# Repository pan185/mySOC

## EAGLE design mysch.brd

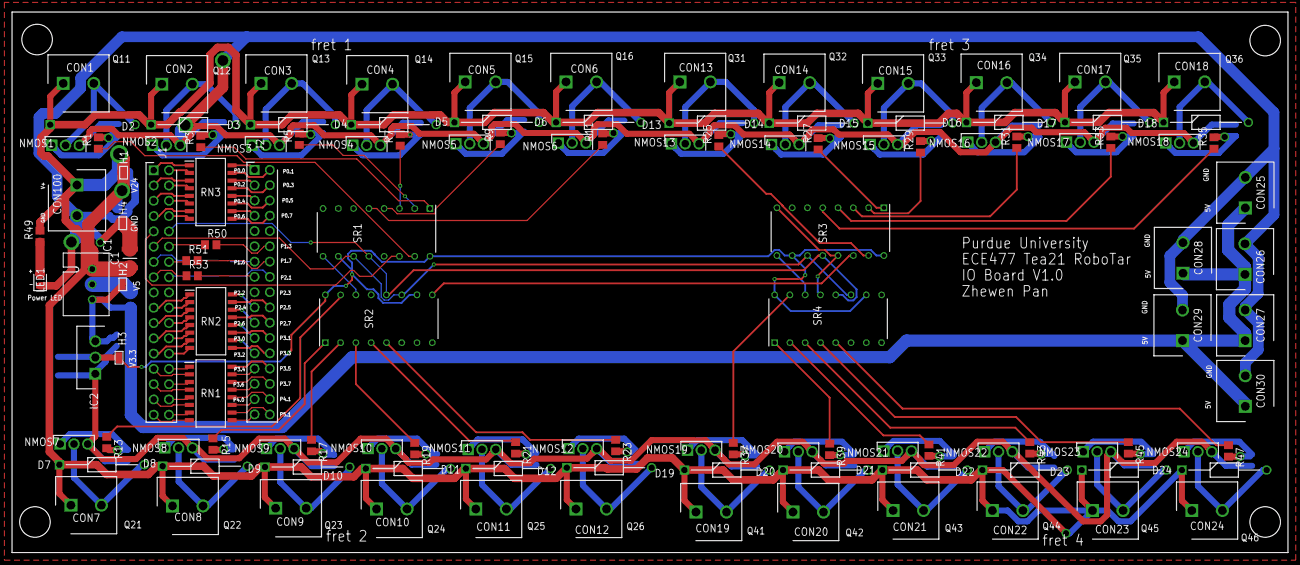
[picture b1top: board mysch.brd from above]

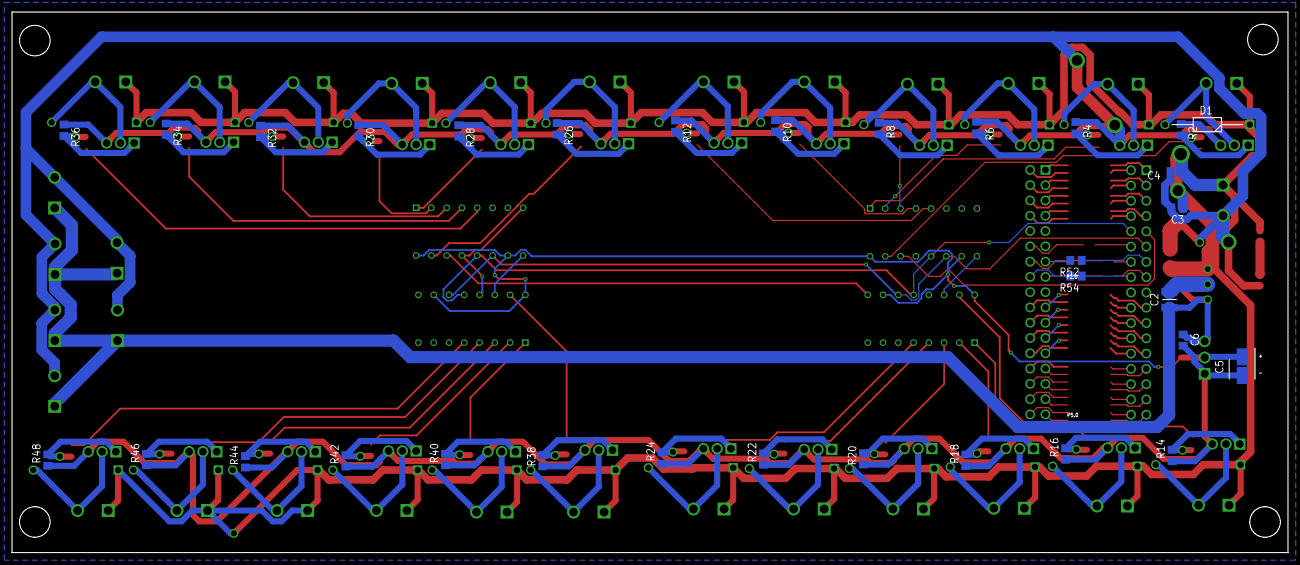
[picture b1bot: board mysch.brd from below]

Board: 2 copper layers, 212.1 x 89.8 mm, 155 parts (32 on the bottom side), 141 nets.

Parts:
C1: 10u; CAPC3225X270N
C2: 22u; CAPC3225X270N
C3: 1u; C0805
C4: 0.1u; C0805
C5: 865080540004; CAPAE430X550N
C6: 100n; C0805
CON1, CON2, CON3, CON4, CON5, CON6, CON7, CON8, CON9, CON10, CON11, CON12, CON13, CON14, CON15, CON16, CON17, CON18, CON19, CON20, CON21, CON22, CON23, CON24, CON25, CON26, CON27, CON28, CON29, CON30, CON100: 1888687; SHDR2W90P0X508_1X2_1016X950X15
D1, D2, D3, D4, D5, D6, D7, D8, D9, D10, D11, D12, D13, D14, D15, D16, D17, D18, D19, D20, D21, D22, D23, D24: 1N4007; DIOAD1410W86L470D235
H1, H2, H3, H4: S2761-46R; S276146R
IC1: OKI-78SR-5_1.5-W36-C; OKI-78SR
IC2: LD1117AV33; TO270P460X1020X2008-3P
J1, J2: 90131-0937; HDRV34W90P254_2X17_4308X500X56
LED1: SML-H12U8TT86C; LEDC2012X90N
NMOS1, NMOS2, NMOS3, NMOS4, NMOS5, NMOS6, NMOS7, NMOS8, NMOS9, NMOS10, NMOS11, NMOS12, NMOS13, NMOS14, NMOS15, NMOS16, NMOS17, NMOS18, NMOS19, NMOS20, NMOS21, NMOS22, NMOS23, NMOS24: RFD3055LE; TO229P250X658X985-3P
R1, R3, R5, R7, R9, R11, R13, R15, R17, R19, R21, R23, R25, R27, R29, R31, R33, R35, R37, R39, R41, R43, R45, R47: 1M; R0805
R2, R4, R6, R8, R10, R12, R14, R16, R18, R20, R22, R24, R26, R28, R30, R32, R34, R36, R38, R40, R42, R44, R46, R48: 3.3k; R0805
R49: 1.1k; R0805
R50, R51, R52, R53, R54: 100; R0805
RN1, RN2, RN3: 4816P-T01-101LF; SOIC127P762X215-16N
SR1, SR2, SR3, SR4: SN74HC595N; DIP794W53P254L1930H508Q16N

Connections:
GND: C1.1, C2.1, C3.2, C4.2, C5.2, C6.2, CON25.2, CON26.2, CON27.2, CON28.2, CON29.2, CON30.2, CON100.2, H4.1, IC1.2, IC2.1, LED1.1, NMOS1.3, NMOS2.3, NMOS3.3, NMOS4.3, NMOS5.3, NMOS6.3, NMOS7.3, NMOS8.3, NMOS9.3, NMOS10.3, NMOS11.3, NMOS12.3, NMOS13.3, NMOS14.3, NMOS15.3, NMOS16.3, NMOS17.3, NMOS18.3, NMOS19.3, NMOS20.3, NMOS21.3, NMOS22.3, NMOS23.3, NMOS24.3, R2.1, R4.1, R6.1, R8.1, R10.1, R12.1, R14.1, R16.1, R18.1, R20.1, R22.1, R24.1, R26.1, R28.1, R30.1, R32.1, R34.1, R36.1, R38.1, R40.1, R42.1, R44.1, R46.1, R48.1, SR1.8, SR1.13, SR2.8, SR2.13, SR3.8, SR3.13, SR4.8, SR4.13
unnamed: CON11.2, D11.2, NMOS11.2
unnamed: NMOS11.1, R21.2, R22.2
unnamed: CON12.2, D12.2, NMOS12.2
unnamed: NMOS12.1, R23.2, R24.2
unnamed: CON14.2, D14.2, NMOS14.2
unnamed: NMOS1.1, R1.2, R2.2
unnamed: CON1.2, D1.2, NMOS1.2
unnamed: CON13.2, D13.2, NMOS13.2
unnamed: NMOS14.1, R27.2, R28.2
unnamed: CON15.2, D15.2, NMOS15.2
unnamed: CON2.2, D2.2, NMOS2.2
unnamed: NMOS2.1, R3.2, R4.2
unnamed: NMOS15.1, R29.2, R30.2
unnamed: CON3.2, D3.2, NMOS3.2
unnamed: NMOS3.1, R5.2, R6.2
unnamed: CON16.2, D16.2, NMOS16.2
unnamed: CON4.2, D4.2, NMOS4.2
unnamed: NMOS4.1, R7.2, R8.2
unnamed: NMOS16.1, R31.2, R32.2
unnamed: CON5.2, D5.2, NMOS5.2
unnamed: NMOS5.1, R9.2, R10.2
unnamed: CON17.2, D17.2, NMOS17.2
unnamed: CON6.2, D6.2, NMOS6.2
unnamed: NMOS6.1, R11.2, R12.2
unnamed: NMOS17.1, R33.2, R34.2
unnamed: CON7.2, D7.2, NMOS7.2
unnamed: NMOS7.1, R13.2, R14.2
unnamed: CON18.2, D18.2, NMOS18.2
unnamed: CON8.2, D8.2, NMOS8.2
unnamed: NMOS8.1, R15.2, R16.2
unnamed: NMOS18.1, R35.2, R36.2
unnamed: CON9.2, D9.2, NMOS9.2
unnamed: NMOS9.1, R17.2, R18.2
unnamed: CON19.2, D19.2, NMOS19.2
unnamed: CON10.2, D10.2, NMOS10.2
unnamed: NMOS10.1, R19.2, R20.2
unnamed: NMOS19.1, R37.2, R38.2
unnamed: CON20.2, D20.2, NMOS20.2
unnamed: NMOS20.1, R39.2, R40.2
unnamed: CON21.2, D21.2, NMOS21.2
unnamed: NMOS21.1, R41.2, R42.2
unnamed: CON22.2, D22.2, NMOS22.2
unnamed: NMOS22.1, R43.2, R44.2
unnamed: NMOS13.1, R25.2, R26.2
unnamed: CON23.2, D23.2, NMOS23.2
unnamed: NMOS23.1, R45.2, R46.2
unnamed: CON24.2, D24.2, NMOS24.2
unnamed: NMOS24.1, R47.2, R48.2
unnamed: LED1.2, R49.1
OUT1: SR1.9, SR2.14
OUT2: SR2.9, SR3.14
OUT3: SR3.9, SR4.14
P0.0: J1.1, RN3.1
P0.0_O: J2.1, RN3.16
P0.1: J1.2, RN3.2
P0.1_O: J2.2, RN3.15
P0.2: J1.3, RN3.3
P0.2_O: J2.3, RN3.14
P0.3: J1.4, RN3.4
P0.3_O: J2.4, RN3.13
P0.4: J1.5, RN3.5
P0.4_O: J2.5, RN3.12
P0.5: J1.6, RN3.6
P0.5_O: J2.6, RN3.11
P0.6: J1.7, RN3.7
P0.6_O: J2.7, RN3.10
P0.7: J1.8, RN3.8
P0.7_O: J2.8, RN3.9
P1.0: J1.9, SR1.14
P1.1: J1.10, SR1.12, SR2.12, SR3.12, SR4.12
P1.2: J1.11, SR1.11, SR2.11, SR3.11, SR4.11
P1.3: J1.12, R50.1
P1.3_O: J2.12, R50.2
P1.6: J1.13, R52.1
P1.6_O: J2.13, R52.2
P1.7: J1.14, R51.1
P1.7_O: J2.14, R51.2
P2.0: J1.15, R53.1
P2.0_O: J2.15, R53.2
P2.1: J1.16, R54.1
P2.1_O: J2.16, R54.2
P2.4: J1.19, RN2.1
P2.4_O: J2.19, RN2.16
P2.5: J1.20, RN2.2
P2.5_O: J2.20, RN2.15
P2.6: J1.21, RN2.3
P2.6_O: J2.21, RN2.14
P2.7: J1.22, RN2.4
P2.7_O: J2.22, RN2.13
P3.0: J1.23, RN2.5
P3.0_O: J2.23, RN2.12
P3.1: J1.24, RN2.6
P3.1_O: J2.24, RN2.11
P3.2: J1.25, RN2.7
P3.2_O: J2.25, RN2.10
P3.3: J1.26, RN2.8
P3.3_O: J2.26, RN2.9
P3.4: J1.27, RN1.2
P3.4_O: J2.27, RN1.15
P3.5: J1.28, RN1.1
P3.5_O: J2.28, RN1.16
P3.6: J1.29, RN1.4
P3.6_O: J2.29, RN1.13
P3.7: J1.30, RN1.3
P3.7_O: J2.30, RN1.14
P4.0: J1.31, RN1.6
P4.0_O: J2.31, RN1.11
P4.1: J1.32, RN1.5
P4.1_O: J2.32, RN1.12
P5.0: J1.33, RN1.8
P5.0_O: J2.33, RN1.9
P5.1: J1.34, RN1.7
P5.1_O: J2.34, RN1.10
Q11: R1.1, SR1.15
Q12: R3.1, SR1.1
Q13: R5.1, SR1.2
Q14: R7.1, SR1.3
Q15: R9.1, SR1.4
Q16: R11.1, SR1.5
Q21: R13.1, SR2.15
Q22: R15.1, SR2.1
Q23: R17.1, SR2.2
Q24: R19.1, SR2.3
Q25: R21.1, SR2.4
Q26: R23.1, SR2.5
Q31: R25.1, SR3.15
Q32: R27.1, SR3.1
Q33: R29.1, SR3.2
Q34: R31.1, SR3.3
Q35: R33.1, SR3.4
Q36: R35.1, SR3.5
Q41: R37.1, SR4.15
Q42: R39.1, SR4.1
Q43: R41.1, SR4.2
Q44: R43.1, SR4.3
Q45: R45.1, SR4.4
Q46: R47.1, SR4.5
V3.3: C5.1, H3.1, IC2.2, SR1.10, SR1.16, SR2.10, SR2.16, SR3.10, SR3.16, SR4.10, SR4.16
V5: C2.2, C6.1, CON25.1, CON26.1, CON27.1, CON28.1, CON29.1, CON30.1, H2.1, IC1.3, IC2.3
V24: C1.2, C3.1, C4.1, CON1.1, CON2.1, CON3.1, CON4.1, CON5.1, CON6.1, CON7.1, CON8.1, CON9.1, CON10.1, CON11.1, CON12.1, CON13.1, CON14.1, CON15.1, CON16.1, CON17.1, CON18.1, CON19.1, CON20.1, CON21.1, CON22.1, CON23.1, CON24.1, CON100.1, D1.1, D2.1, D3.1, D4.1, D5.1, D6.1, D7.1, D8.1, D9.1, D10.1, D11.1, D12.1, D13.1, D14.1, D15.1, D16.1, D17.1, D18.1, D19.1, D20.1, D21.1, D22.1, D23.1, D24.1, H1.1, IC1.1, R49.2

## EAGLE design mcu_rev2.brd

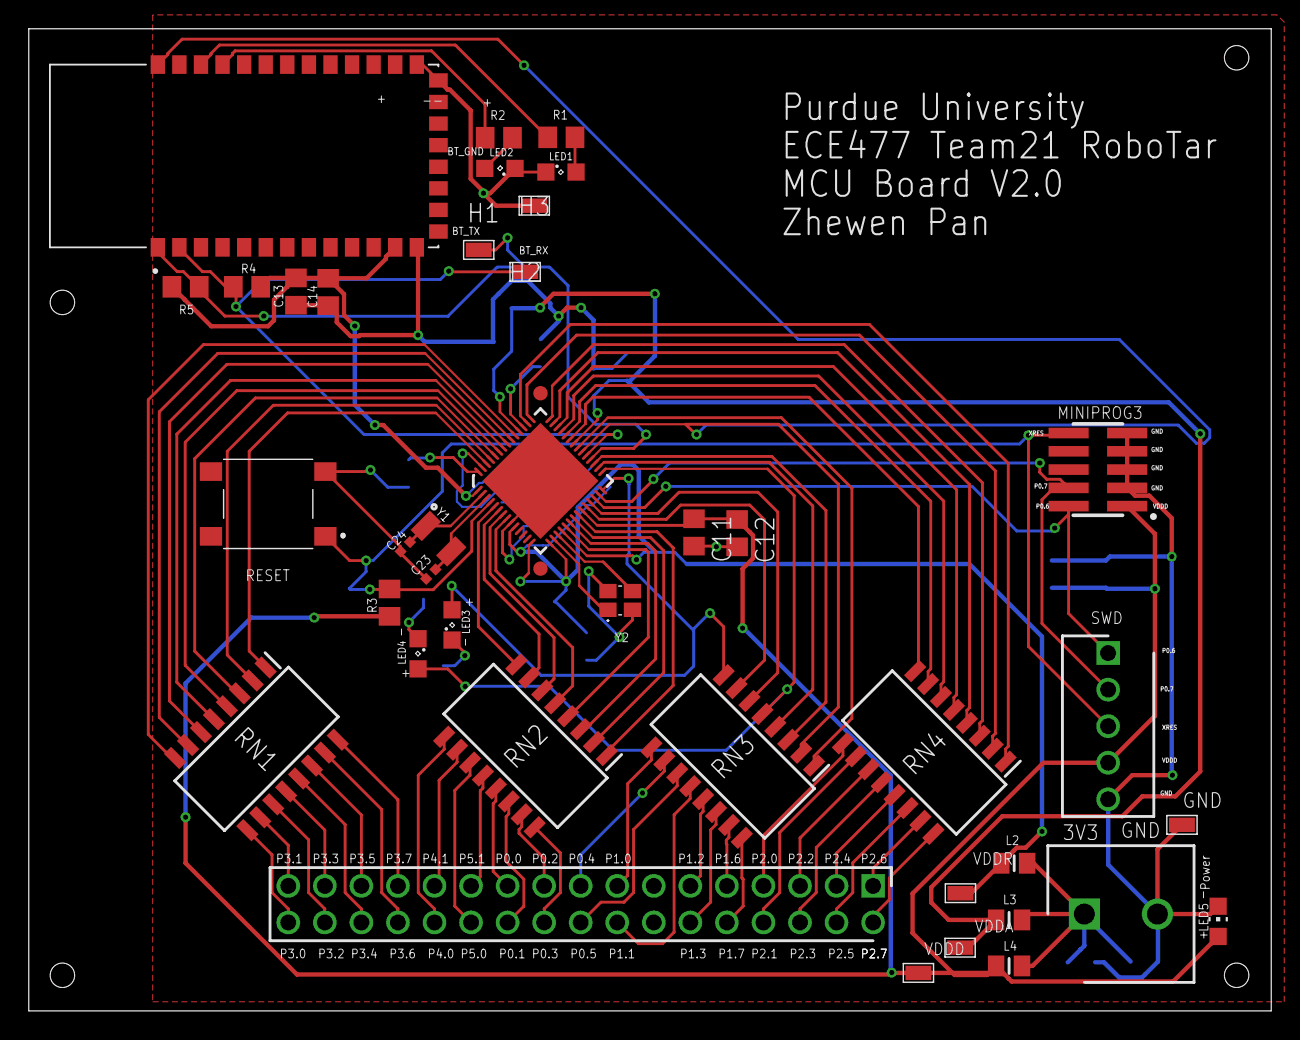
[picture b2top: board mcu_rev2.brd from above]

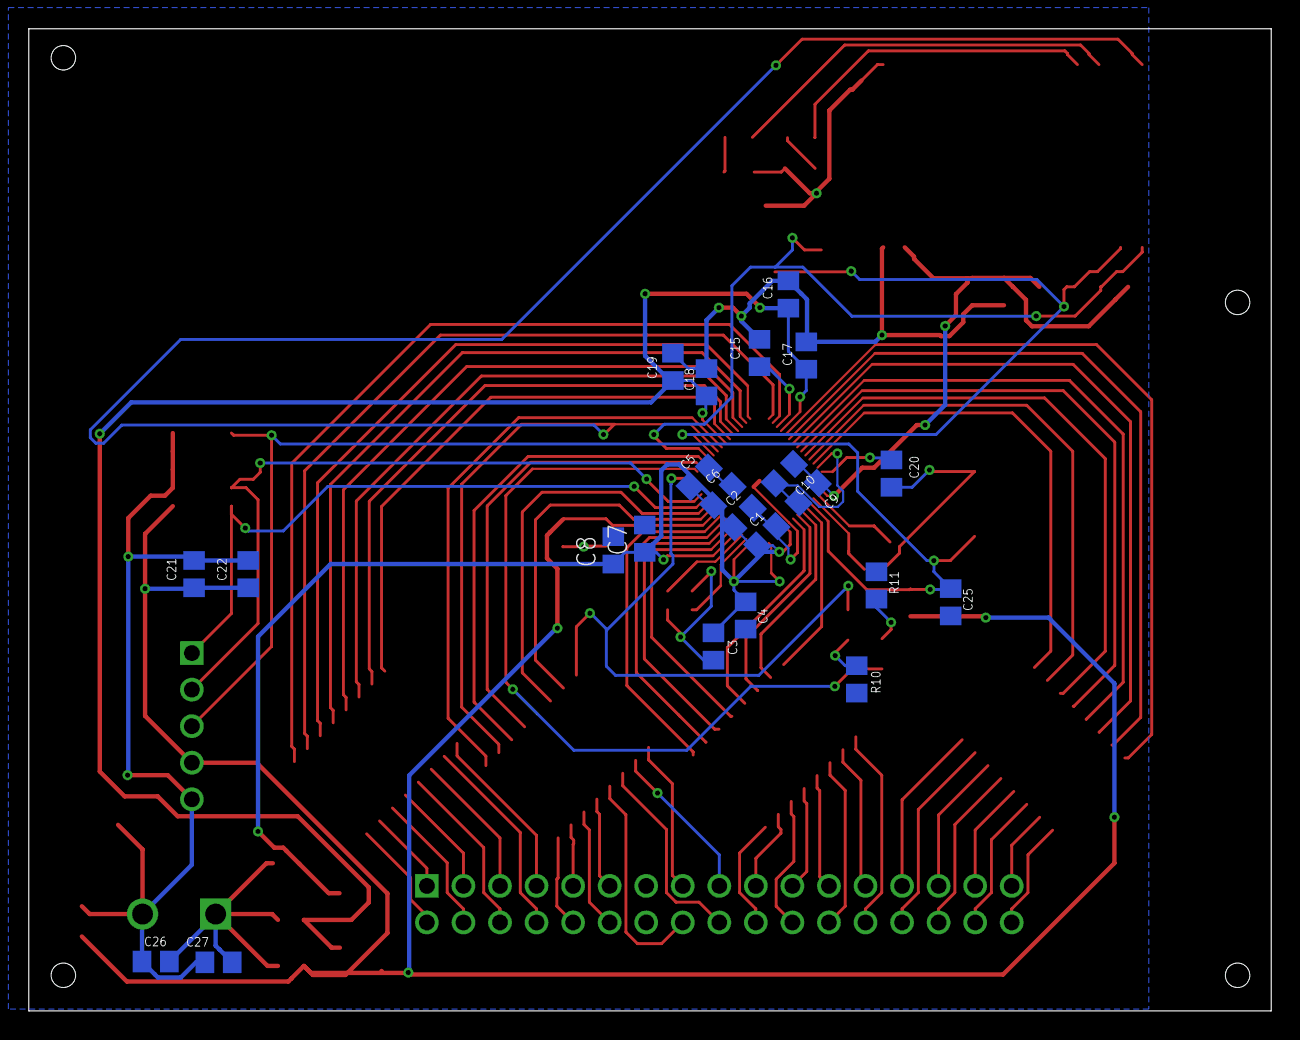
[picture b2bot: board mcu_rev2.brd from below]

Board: 2 copper layers, 86.3 x 68.2 mm, 62 parts (23 on the bottom side), 86 nets.

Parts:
BT_SLAVE: HC-05; XCVR_HC-05
C1, C3, C5, C7, C9, C11, C13, C16, C18, C21, C27: 0.1u; C0805
C2, C4, C6, C8, C10, C12, C14, C17, C19, C20, C22, C26: 1u; C0805
C15: 1uF; C0805
C23: 36p; CAPC1005X55N
C24: 18p; CAPC1005X55N
C25: 100p; C0805
CON1: 1888687; SHDR2W90P0X508_1X2_1016X950X15
H1, H2, H3, H4, H5, H6, H7: S2761-46R; S276146R
IC1: CY8C4248LQI-BL583; QFN40P700X700X60-57N
J1: MINIPROG3; FTSH-105-01-L-DV-K
J2: SWD; HDRV5W64P0X254_1X5_1255X635X81
J3: 90131-0937; HDRV34W90P254_2X17_4308X500X56
L2, L3, L4: 330ohm, 100MHz; BEADC2012X105N
LED1, LED2, LED3, LED4: 0; SML0805
LED5: 0; CHIP-LED0805
R1, R2: 470; R0805
R3, R4: 4.7k; R0805
R5: 10k; R0805
R10, R11: 1.5k; R0805
RN1, RN2, RN3, RN4: 4816P-T01-101LF; SOIC127P762X215-16N
S1: DTSM-63N-V-B; DTSM63NVB
Y1: 32.768KHz; ECX-31B
Y2: 24MHz; ECS240836QAESTR

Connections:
3V3: C26.1, C27.1, CON1.1, L2.1, L3.1, L4.1
/XRES: C25.1, IC1.4, J1.10, J2.3, R3.1, S1.1
GND: BT_SLAVE.13, BT_SLAVE.21, BT_SLAVE.22, C1.2, C2.2, C3.2, C4.2, C5.2, C6.2, C7.2, C8.2, C9.2, C10.2, C11.2, C12.2, C13.2, C14.2, C15.2, C16.2, C17.2, C18.2, C19.2, C20.2, C21.2, C22.2, C23.1, C24.1, C25.2, C26.2, C27.2, CON1.2, H3.1, H7.1, IC1.9, IC1.55, IC1.57, J1.3, J1.5, J1.7, J1.9, J2.5, LED1.C, LED2.C, LED5.C, R10.2, R11.2, S1.3, Y2.2, Y2.4
IND1: BT_SLAVE.32, R1.1
IND2: BT_SLAVE.31, R2.1
MID1: LED1.A, R1.2
MID2: LED2.A, R2.2
unnamed: LED3.C, R10.1
unnamed: LED4.C, R11.1
P0.0: IC1.19, RN2.4
P0.0_O: J3.21, RN2.13
P0.1: IC1.20, RN2.3
P0.1_O: J3.22, RN2.14
P0.2: IC1.21, RN2.2
P0.2_O: J3.19, RN2.15
P0.3: IC1.22, RN2.1
P0.3_O: J3.20, RN2.16
P0.4: IC1.24, RN3.7
P0.4_O: J3.17, RN3.10
P0.5: IC1.25, RN3.6
P0.5_O: J3.18, RN3.11
P0.6: IC1.26, J1.2, J2.1
P0.7: IC1.27, J1.4, J2.2
P1.0: IC1.28, LED3.A, RN3.8
P1.0_O: J3.15, RN3.9
P1.1: IC1.29, LED4.A, RN3.5
P1.1_O: J3.16, RN3.12
P1.2: IC1.30, RN3.4
P1.2_O: J3.11, RN3.13
P1.3: IC1.31, RN3.3
P1.3_O: J3.12, RN3.14
P1.4: BT_SLAVE.1, H1.1, IC1.32, R5.1
P1.5: BT_SLAVE.2, H2.1, IC1.33, R4.1
P1.6: BT_SLAVE.34, IC1.34, RN3.2
P1.6_O: J3.9, RN3.15
P1.7: IC1.35, RN3.1
P1.7_O: J3.10, RN3.16
P2.0: IC1.37, RN4.8
P2.0_O: J3.7, RN4.9
P2.1: IC1.38, RN4.7
P2.1_O: J3.8, RN4.10
P2.2: IC1.39, RN4.6
P2.2_O: J3.5, RN4.11
P2.3: IC1.40, RN4.5
P2.3_O: J3.6, RN4.12
P2.4: IC1.41, RN4.4
P2.4_O: J3.3, RN4.13
P2.5: IC1.42, RN4.3
P2.5_O: J3.4, RN4.14
P2.6: IC1.43, RN4.2
P2.6_O: J3.1, RN4.15
P2.7: IC1.44, RN4.1
P2.7_O: J3.2, RN4.16
P3.0: IC1.47, RN1.8
P3.0_O: J3.34, RN1.9
P3.1: IC1.48, RN1.7
P3.1_O: J3.33, RN1.10
P3.2: IC1.49, RN1.6
P3.2_O: J3.32, RN1.11
P3.3: IC1.50, RN1.5
P3.3_O: J3.31, RN1.12
P3.4: IC1.51, RN1.4
P3.4_O: J3.30, RN1.13
P3.5: IC1.52, RN1.3
P3.5_O: J3.29, RN1.14
P3.6: IC1.53, RN1.2
P3.6_O: J3.28, RN1.15
P3.7: IC1.54, RN1.1
P3.7_O: J3.27, RN1.16
P4.0: IC1.5, RN2.8
P4.0_O: J3.26, RN2.9
P4.1: IC1.6, RN2.7
P4.1_O: J3.25, RN2.10
P5.0: IC1.7, RN2.6
P5.0_O: J3.24, RN2.11
P5.1: IC1.8, RN2.5
P5.1_O: J3.23, RN2.12
P6.0: C24.2, IC1.2, Y1.1
P6.1: C23.2, IC1.3, Y1.2
VCCD: C20.1, IC1.56
VDDA: C16.1, C17.1, C18.1, C19.1, H5.1, IC1.36, IC1.46, L3.2
VDDD: BT_SLAVE.12, C9.1, C10.1, C11.1, C12.1, C13.1, C14.1, C21.1, C22.1, H4.1, IC1.1, IC1.23, J1.1, J2.4, L4.2, LED5.A, R3.2, R4.2, R5.2
VDDR: C1.1, C2.1, C3.1, C4.1, C5.1, C6.1, C7.1, C8.1, H6.1, IC1.10, IC1.14, IC1.15, IC1.18, L2.2
VREF: C15.1, IC1.45
XTAL24I: IC1.16, Y2.1
XTAL24O: IC1.17, Y2.3

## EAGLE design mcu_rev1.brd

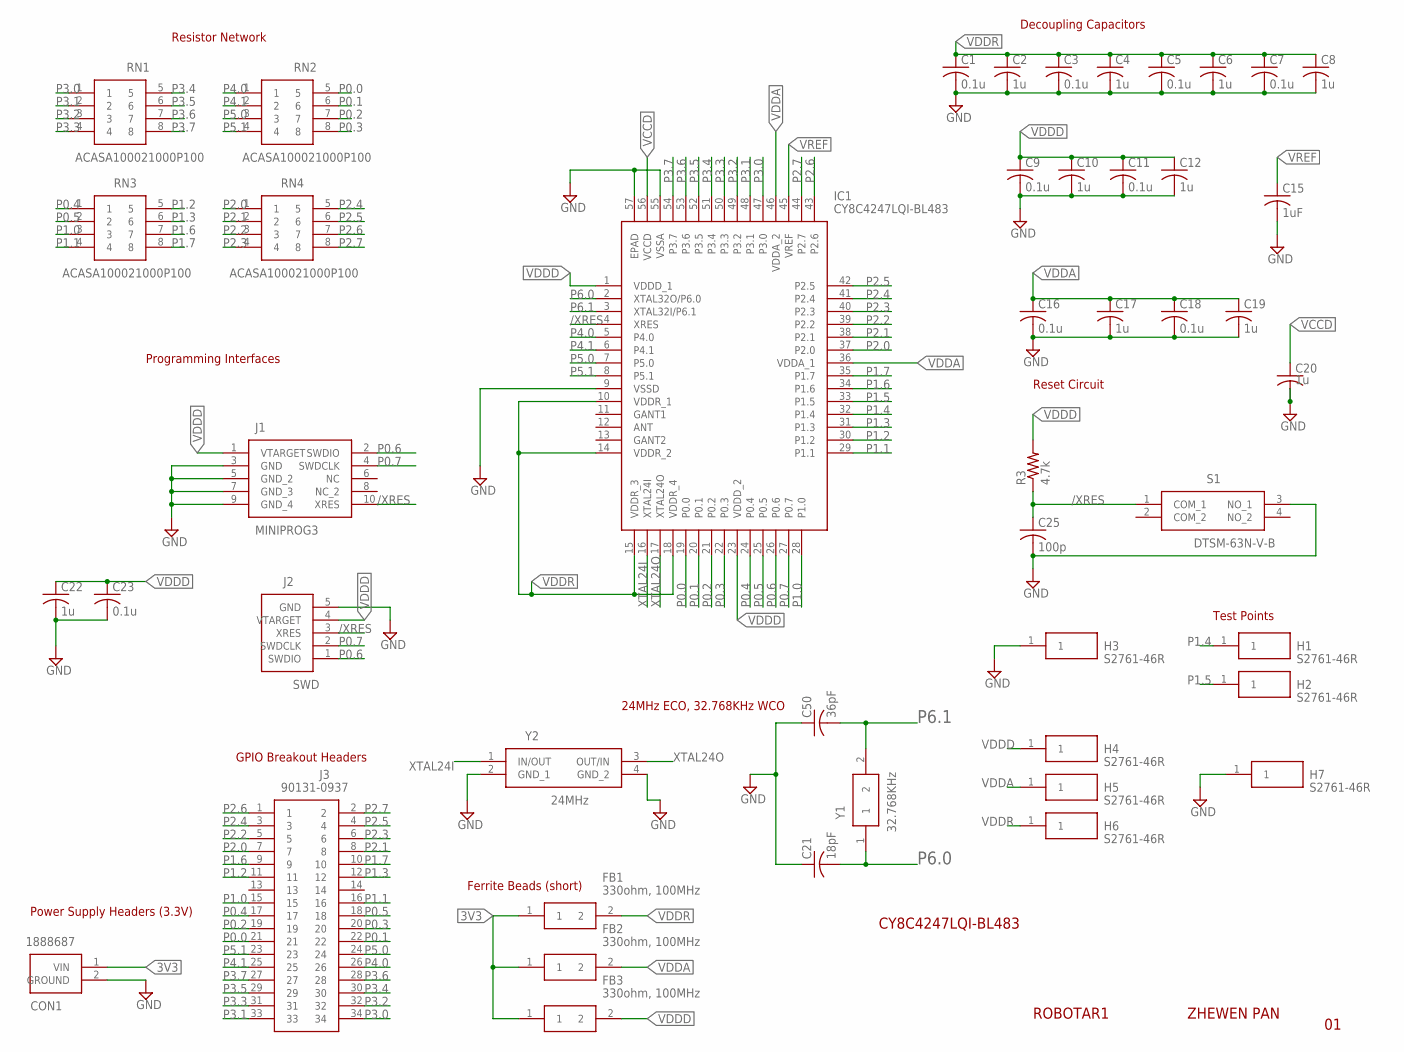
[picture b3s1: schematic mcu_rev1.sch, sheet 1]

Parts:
C1, C3, C5, C7, C9, C11, C16, C18, C23: 0.1u; C0805
C2, C4, C6, C8, C10, C12, C17, C19, C20, C22: 1u; C0805
C15: 1uF; C0805
C21: 18pF; C0805
C25: 100p; C0805
C50: 36pF; C0805
CON1: 1888687; SHDR2W90P0X508_1X2_1016X950X15
FB1, FB2, FB3: 330ohm, 100MHz; BEADC2012X105N
H1, H2, H3, H4, H5, H6, H7: S2761-46R; S276146R
IC1: CY8C4247LQI-BL483; QFN40P700X700X60-57N
J1: MINIPROG3; FTSH-105-01-L-DV-K
J2: SWD; HDRV5W64P0X254_1X5_1255X635X81
J3: 90131-0937; HDRV34W90P254_2X17_4308X500X56
R3: 4.7k; R0805
RN1, RN2, RN3, RN4: ACASA100021000P100
S1: DTSM-63N-V-B; DTSM63NVB
Y1: 32.768KHz; ECX-31B
Y2: 24MHz; ECS240836QAESTR

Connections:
3V3: CON1.1 (VIN), FB1.1, FB2.1, FB3.1
/XRES: C25.1, IC1.4 (XRES), J1.10 (XRES), J2.3 (XRES), R3.1, S1.1 (COM_1)
GND: C1.2, C2.2, C3.2, C4.2, C5.2, C6.2, C7.2, C8.2, C9.2, C10.2, C11.2, C12.2, C15.2, C16.2, C17.2, C18.2, C19.2, C20.2, C21.1, C22.2, C23.2, C25.2, C50.1, CON1.2 (GROUND), H3.1, H7.1, IC1.9 (VSSD), IC1.55 (VSSA), IC1.57 (EPAD), J1.3 (GND), J1.5 (GND_2), J1.7 (GND_3), J1.9 (GND_4), J2.5 (GND), S1.3 (NO_1), Y2.2 (GND_1), Y2.4 (GND_2); also elsewhere on the board
P0.0: IC1.19 (P0.0), J3.21, RN2.5
P0.1: IC1.20 (P0.1), J3.22, RN2.6
P0.2: IC1.21 (P0.2), J3.19, RN2.7
P0.3: IC1.22 (P0.3), J3.20, RN2.8
P0.4: IC1.24 (P0.4), J3.17, RN3.1
P0.5: IC1.25 (P0.5), J3.18, RN3.2
P0.6: IC1.26 (P0.6), J1.2 (SWDIO), J2.1 (SWDIO)
P0.7: IC1.27 (P0.7), J1.4 (SWDCLK), J2.2 (SWDCLK)
P1.0: IC1.28 (P1.0), J3.15, RN3.3
P1.1: IC1.29 (P1.1), J3.16, RN3.4
P1.2: IC1.30 (P1.2), J3.11, RN3.5
P1.3: IC1.31 (P1.3), J3.12, RN3.6
P1.4: H1.1, IC1.32 (P1.4); also elsewhere on the board
P1.5: H2.1, IC1.33 (P1.5); also elsewhere on the board
P1.6: IC1.34 (P1.6), J3.9, RN3.7; also elsewhere on the board
P1.7: IC1.35 (P1.7), J3.10, RN3.8
P2.0: IC1.37 (P2.0), J3.7, RN4.1
P2.1: IC1.38 (P2.1), J3.8, RN4.2
P2.2: IC1.39 (P2.2), J3.5, RN4.3
P2.3: IC1.40 (P2.3), J3.6, RN4.4
P2.4: IC1.41 (P2.4), J3.3, RN4.5
P2.5: IC1.42 (P2.5), J3.4, RN4.6
P2.6: IC1.43 (P2.6), J3.1, RN4.7
P2.7: IC1.44 (P2.7), J3.2, RN4.8
P3.0: IC1.47 (P3.0), J3.34, RN1.1
P3.1: IC1.48 (P3.1), J3.33, RN1.2
P3.2: IC1.49 (P3.2), J3.32, RN1.3
P3.3: IC1.50 (P3.3), J3.31, RN1.4
P3.4: IC1.51 (P3.4), J3.30, RN1.5
P3.5: IC1.52 (P3.5), J3.29, RN1.6
P3.6: IC1.53 (P3.6), J3.28, RN1.7
P3.7: IC1.54 (P3.7), J3.27, RN1.8
P4.0: IC1.5 (P4.0), J3.26, RN2.1
P4.1: IC1.6 (P4.1), J3.25, RN2.2
P5.0: IC1.7 (P5.0), J3.24, RN2.3
P5.1: IC1.8 (P5.1), J3.23, RN2.4
P6.0: C21.2, IC1.2 (XTAL32O/P6.0), Y1.1
P6.1: C50.2, IC1.3 (XTAL32I/P6.1), Y1.2
VCCD: C20.1, IC1.56 (VCCD)
VDDA: C16.1, C17.1, C18.1, C19.1, FB2.2, H5.1, IC1.36 (VDDA_1), IC1.46 (VDDA_2)
VDDD: C9.1, C10.1, C11.1, C12.1, C22.1, C23.1, FB3.2, H4.1, IC1.1 (VDDD_1), IC1.23 (VDDD_2), J1.1 (VTARGET), J2.4 (VTARGET), R3.2; also elsewhere on the board
VDDR: C1.1, C2.1, C3.1, C4.1, C5.1, C6.1, C7.1, C8.1, FB1.2, H6.1, IC1.10 (VDDR_1), IC1.14 (VDDR_2), IC1.15 (VDDR_3), IC1.18 (VDDR_4)
VREF: C15.1, IC1.45 (VREF)
XTAL24I: IC1.16 (XTAL24I), Y2.1 (IN/OUT)
XTAL24O: IC1.17 (XTAL24O), Y2.3 (OUT/IN)

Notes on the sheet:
CY8C4247LQI-BL483
ROBOTAR1
ZHEWEN PAN
Programming Interfaces
GPIO Breakout Headers
Power Supply Headers (3.3V)
Ferrite Beads (short)
24MHz ECO, 32.768KHz WCO
Reset Circuit
Test Points
Resistor Network
Decoupling Capacitors

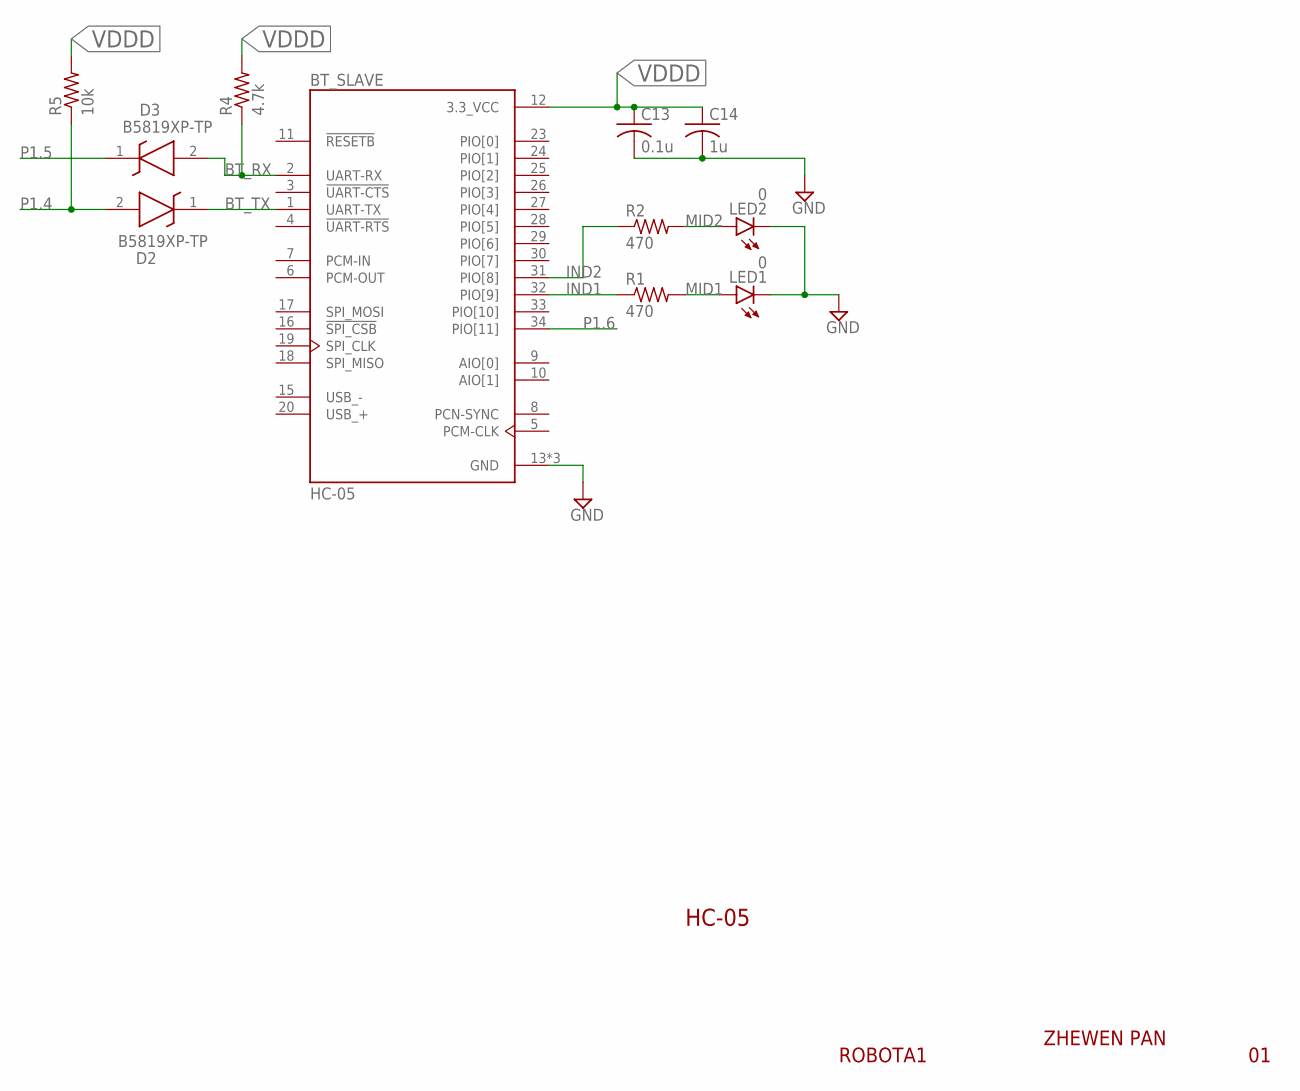
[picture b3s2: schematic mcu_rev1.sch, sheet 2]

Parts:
BT_SLAVE: HC-05; XCVR_HC-05
C13: 0.1u; C0805
C14: 1u; C0805
D2, D3: B5819XP-TP; B5819XPTP
LED1, LED2: 0; SML0805
R1, R2: 470; R0805
R4: 4.7k; R0805
R5: 10k; R0805

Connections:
BT_RX: BT_SLAVE.2 (UART-RX), D3.2 (+), R4.1
BT_TX: BT_SLAVE.1 (UART-TX), D2.1 (-)
GND: BT_SLAVE.13 (GND), BT_SLAVE.21 (GND), BT_SLAVE.22 (GND), C13.2, C14.2, LED1.C, LED2.C; also elsewhere on the board
IND1: BT_SLAVE.32 (PIO[9]), R1.1
IND2: BT_SLAVE.31 (PIO[8]), R2.1
MID1: LED1.A, R1.2
MID2: LED2.A, R2.2
P1.4: D2.2 (+), R5.1; also elsewhere on the board
P1.5: D3.1 (-); also elsewhere on the board
P1.6: BT_SLAVE.34 (PIO[11]); also elsewhere on the board
VDDD: BT_SLAVE.12 (3.3_VCC), C13.1, C14.1, R4.2, R5.2; also elsewhere on the board

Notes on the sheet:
HC-05
ROBOTA1
ZHEWEN PAN

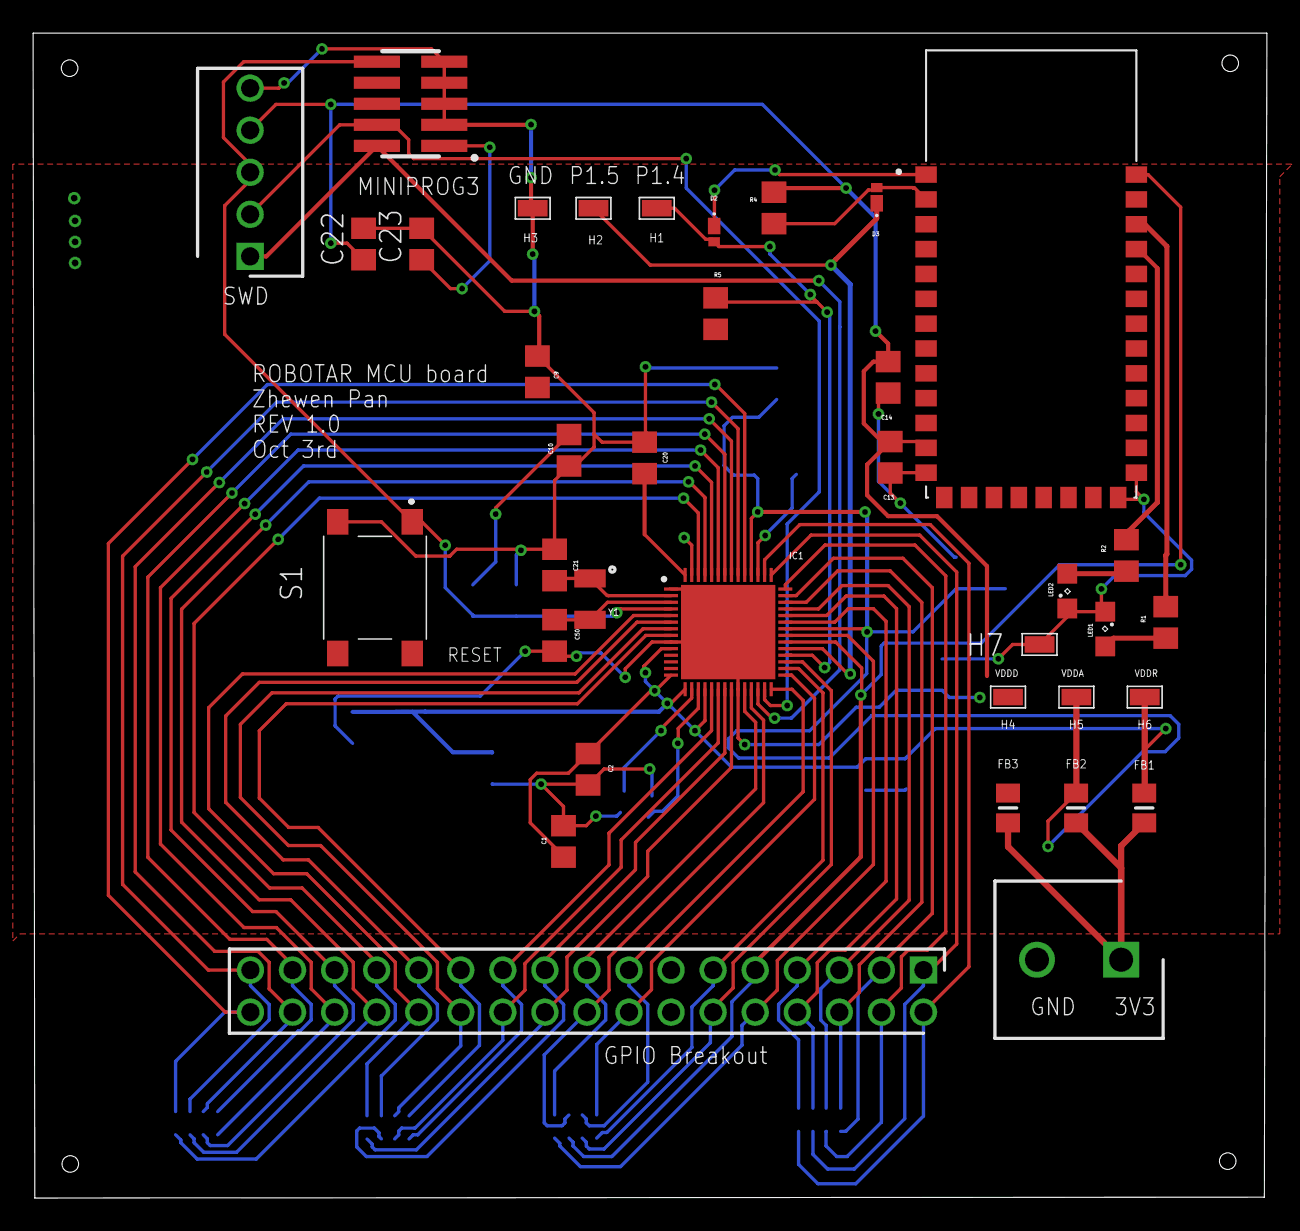
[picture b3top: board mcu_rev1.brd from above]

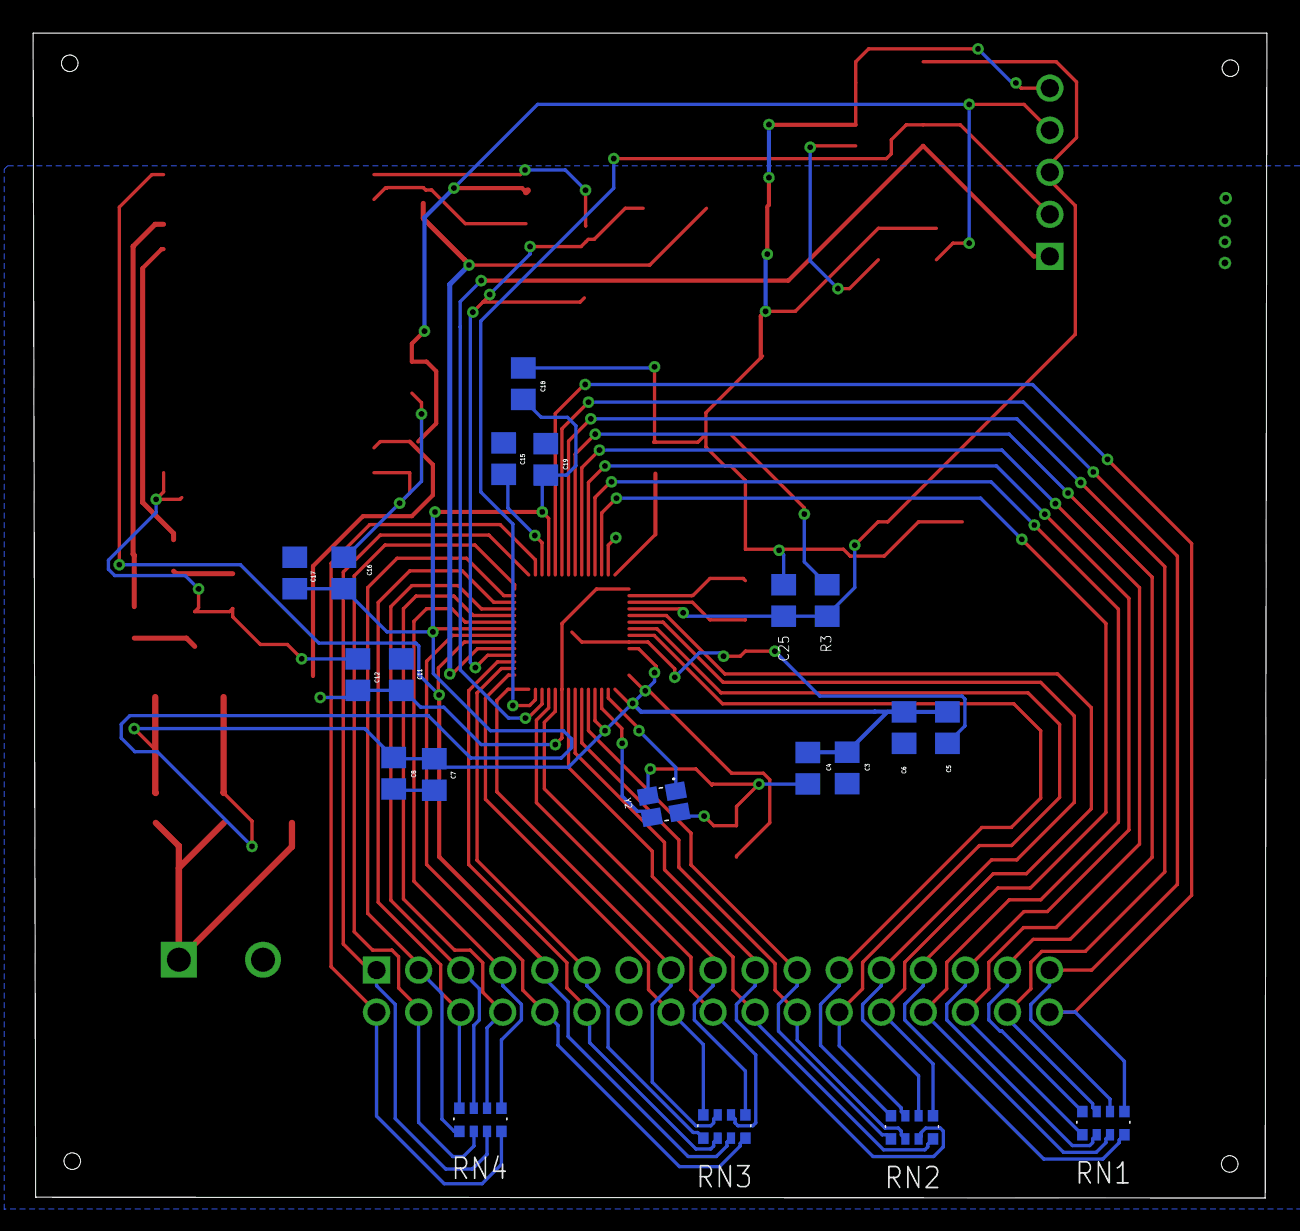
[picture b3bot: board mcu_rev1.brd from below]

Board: 2 copper layers, 74.5 x 70.3 mm, 57 parts (20 on the bottom side), 54 nets.

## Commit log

2019-09-23 started schematic for Cypress PSoC
2019-09-23 selected ECO and WCO
2019-09-26 SWD modified
2019-09-26 more on nmos circuit
2019-09-27 added shift register and nmos switch circuit
2019-10-09 draft 1 finished
2019-10-14 ready for review and fab draft 1
